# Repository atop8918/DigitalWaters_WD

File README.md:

# DigitalWaters_WD
Digital Waters Water Monitoring Device hardware

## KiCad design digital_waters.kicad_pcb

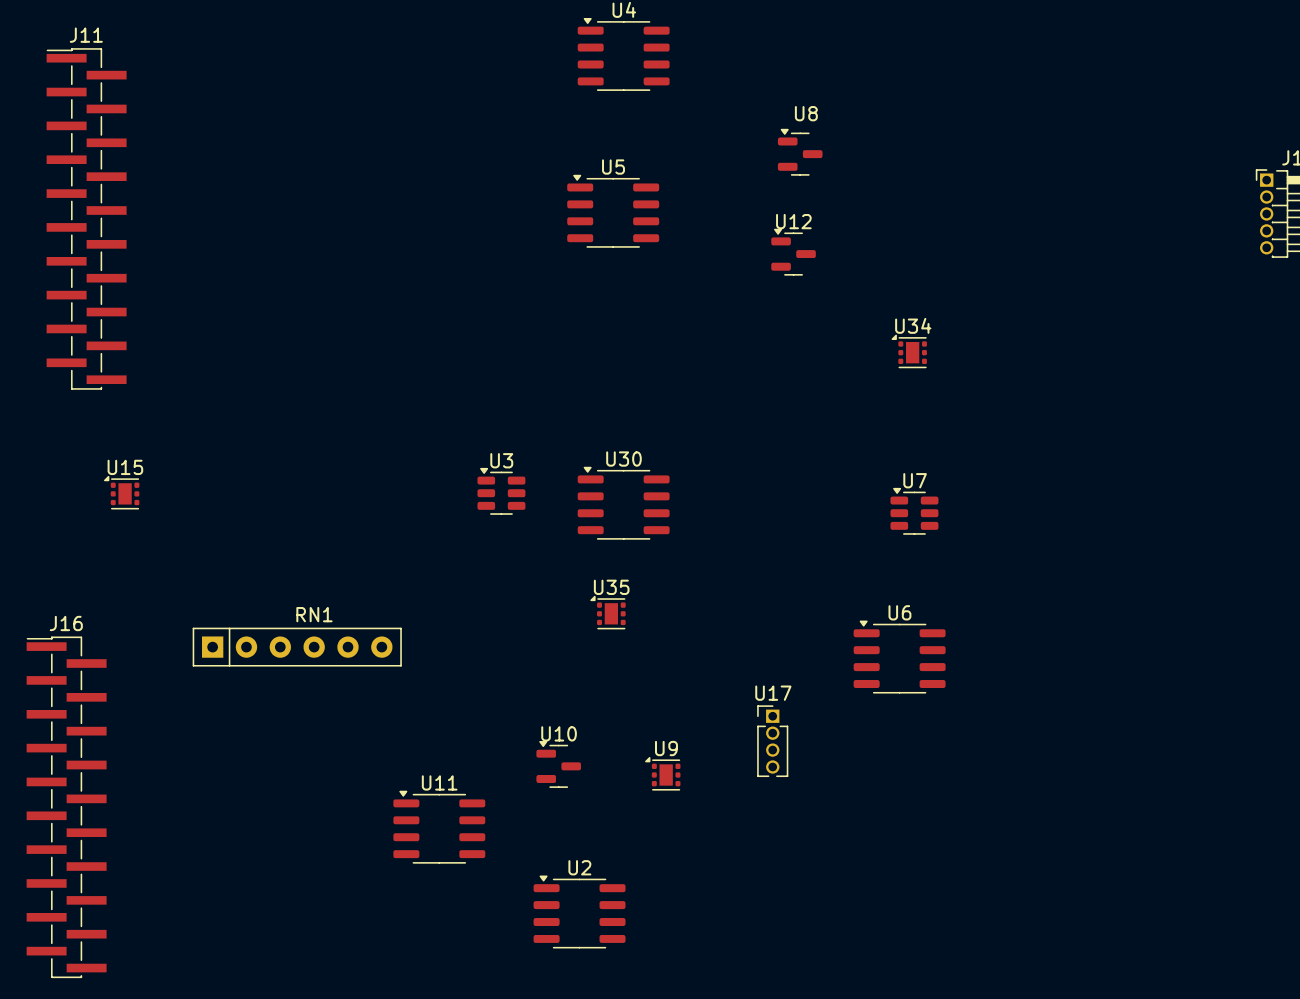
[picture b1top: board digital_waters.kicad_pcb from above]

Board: 2 copper layers, 20 parts (0 on the bottom side), 18 nets, no tracks yet.

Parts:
J11, J16: Conn_01x20_Socket; PinHeader_1x20_P1.27mm_Vertical_SMD_Pin1Left
J18: EZO Carrier Board; PinHeader_1x05_P1.27mm_Horizontal
RN1: R_Pack03_SIP; R_Array_SIP6
U2, U30: TLV2387DR; SOIC-8_3.9x4.9mm_P1.27mm
U3, U7: TPS22929D; SOT-23-6
U4, U5, U11: OPA2397DGKR; SOIC-8_3.9x4.9mm_P1.27mm
U6: M24C02-WMN; SOIC-8_3.9x4.9mm_P1.27mm
U8, U10: REF3040; SOT-23
U9, U15, U34, U35: TVS0500DRV; WSON-6-1EP_2x2mm_P0.65mm_EP1x1.6mm
U12: REF3025; SOT-23
U17: DHT20; PinHeader_1x04_P1.27mm_Vertical

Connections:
+3.3V: J16.1, J16.16, J16.17, J16.18
+5V: J16.19, J16.20, U3.4 (VIN), U3.6 (VIN)
/Base_Sensor/ANALOG_GND: RN1.6 (R3.2), U2.4 (V-), U9.1 (GND), U9.2 (GND), U9.3 (GND), U9.7 (GND), U10.3 (GND), U11.4 (V-)
/Base_Sensor/VDD: U2.3 (+), U2.8 (V+), U3.1 (VOUT), U10.1 (IN), U11.8 (V+)
/Base_Sensor/Vsense: RN1.1 (R1.1), RN1.3 (R2.1)
/Sensor Module Prototype/+2.5V_REF: U12.2 (OUT), U30.3 (+), U30.5 (+)
/Sensor Module Prototype/+5V: U7.4 (VIN), U7.6 (VIN)
/Sensor Module Prototype/ANALOG_GND: U4.4 (V-), U8.3 (GND), U12.3 (GND), U30.4 (V-), U34.1 (GND), U34.2 (GND), U34.3 (GND), U34.7 (GND), U35.1 (GND), U35.2 (GND), U35.3 (GND), U35.7 (GND)
/Sensor Module Prototype/DIGITAL_GND: J18.3, U6.4 (VSS), U7.2 (GND), U7.5 (GND)
/Sensor Module Prototype/I2C_SCL: J18.1, U6.6 (SCL)
/Sensor Module Prototype/I2C_SDA: J18.2, U6.5 (SDA)
/Sensor Module Prototype/Vdd: J18.4, J18.5, U4.8 (V+), U6.8 (VCC), U7.1 (VOUT), U8.1 (IN), U12.1 (IN), U30.8 (V+)
GND: J11.1, J11.2, J11.3, J11.4, J11.9, J11.10, J11.14, J11.20, J16.14, U3.2 (GND), U3.5 (GND), U15.1 (GND), U15.2 (GND), U15.3 (GND), U15.7 (GND)
unnamed: U15.4 (IN), U15.5 (IN), U15.6 (IN)
unnamed: RN1.4 (R2.2), RN1.5 (R3.1)
unnamed: U2.1, U2.2 (-), U9.4 (IN), U9.5 (IN), U9.6 (IN)
unnamed: U30.1, U30.2 (-), U35.4 (IN), U35.5 (IN), U35.6 (IN)
unnamed: U30.6 (-), U30.7, U34.4 (IN), U34.5 (IN), U34.6 (IN)

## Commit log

2025-05-09 Inception Initializing the digital water hardware repo with the schematics so far.
2025-05-09 Adding schematic pdf
2025-05-09 Sensor board basic updates
2025-05-09 Missed update of output.pdf
2025-05-12 Split the sensor modules into a 4 and 8 port version. Fleshed out the power module a bit more. Started adding sensor board connectors to the root schematic and started pulling out sensor boards to th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
2025-05-12 Forgot to update the damn PDF again.
2025-05-12 Figured out which option lets you print the sheets.
2025-05-22 Removed hierarchical labels on the sensor board (4 slot) in favour of local labels and connectors. The idea was that the sensor boards are plug-ins so having them defined as separate boards makes mor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
2025-05-23 Cleaned up some signal lines in the sensor board. Shuffled the decoupling caps around a bit as well as rearranged the EEPROM and power supply for clarity. Added buffered 2.5V offset to the pH and ORP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
2025-05-26 Added some notes to otherwise blank pages. Added the full 8 sensor buffers to the 8 sensor analog board. Added a decoupling sub page to same. Changed a couple of sensor labels on base and 4 board jus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
2025-05-26 Oopsie. - Changed Channel 7 on the analog 8 board to a calibration input. - Added a TODO to the root page
2025-05-29 Updated the ORP and pH probes with a more appropriate amp. Added some notes. Added a tentative PL-100 adapter circuit. Added Vref buffering. Started move towards ESP32 ADC converter for base sensors.
2025-05-30 More notes and comments Cleaned up some signal lines Compacted the decoupling sections Added Turbidity placeholder
2025-05-31 Cleaned up a bit Added a SPDT to calibrate signal on the base board Added PTC and MOV to power section
2025-06-07 Began assigning footprints Cleaned up some of the signalling and added the full prototype sensor suite Added a header for the Atlas Scientific carrier board Added some test points and jumpers Cleaned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
